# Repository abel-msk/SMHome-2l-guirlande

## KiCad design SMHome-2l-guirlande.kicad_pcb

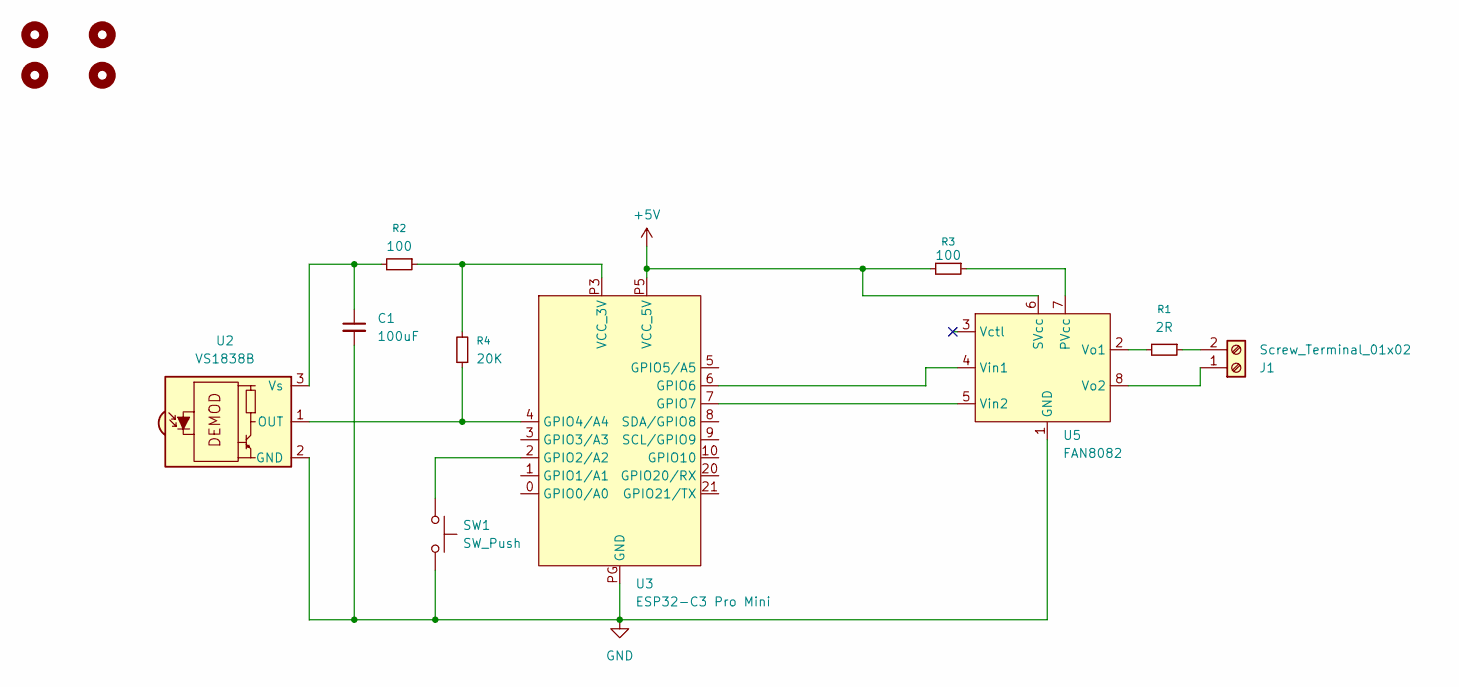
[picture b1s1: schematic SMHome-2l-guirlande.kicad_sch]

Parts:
C1: 100uF; C_1206_3216Metric_Pad1.33x1.80mm_HandSolder
J1: Screw_Terminal_01x02; TerminalBlock_Phoenix_MKDS-1,5-2_1x02_P5.00mm_Horizontal
R1: 2R; R_1210_3225Metric
R2: 100; R_0805_2012Metric_Pad1.20x1.40mm_HandSolder
R3: 100; R_1210_3225Metric_Pad1.30x2.65mm_HandSolder
R4: 20K; R_0805_2012Metric_Pad1.20x1.40mm_HandSolder
SW1: SW_Push; SW_SPST_TL3305A
TP1, TP2, TP3, TP4: MountingHole_2.5mm
U2: VS1838B; Vishay_MOLD-3Pin
U3: ESP32-C3 Pro Mini; ESP32-C3_Pro_mini_pin
U5: FAN8082; DIP-8_W10.16mm

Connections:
+5V: R3.2, U3.P5 (VCC_5V), U5.6 (SVcc)
GND: C1.2, SW1.2, U2.2 (GND), U3.PG (GND), U5.1 (GND)
unnamed: J1.1, U5.8 (Vo2)
unnamed: J1.2, R1.1
unnamed: R4.1, U2.1 (OUT), U3.4 (GPIO4/A4)
unnamed: C1.1, R2.2, U2.3 (Vs)
unnamed: SW1.1, U3.2 (GPIO2/A2)
unnamed: U3.6 (GPIO6), U5.4 (Vin1)
unnamed: U3.7 (GPIO7), U5.5 (Vin2)
unnamed: R2.1, R4.2, U3.P3 (VCC_3V)
unnamed: R3.1, U5.7 (PVcc)
unnamed: R1.2, U5.2 (Vo1)

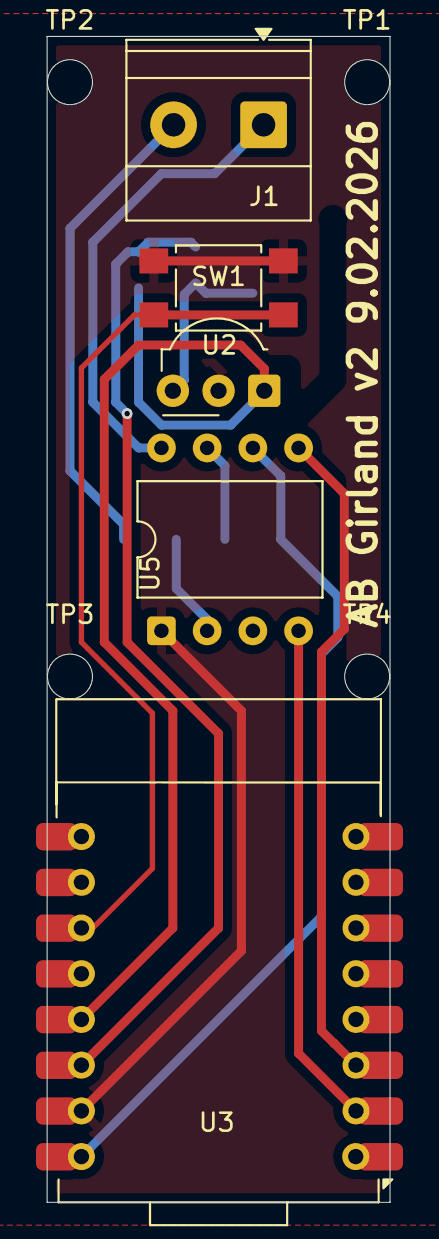
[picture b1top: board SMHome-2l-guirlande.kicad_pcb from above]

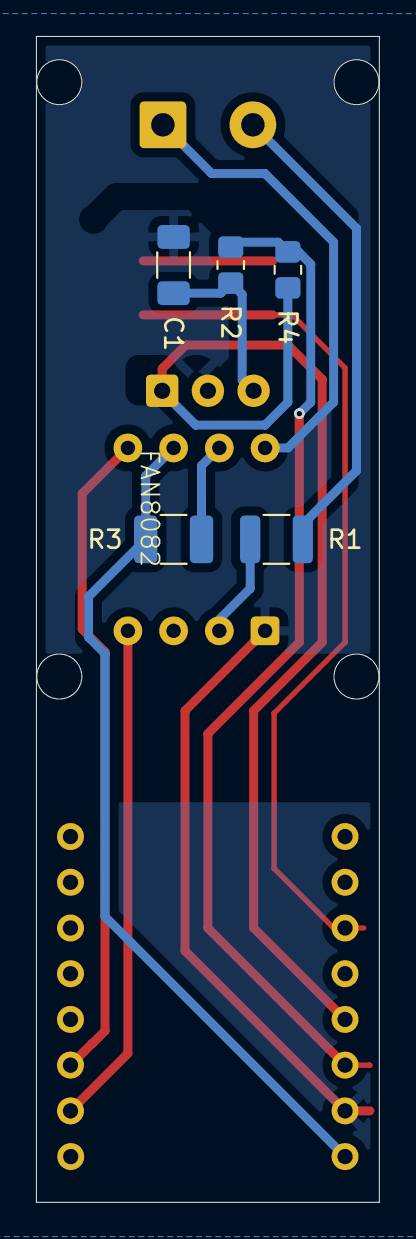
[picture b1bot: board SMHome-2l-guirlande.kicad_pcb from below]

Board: 2 copper layers, 19.0 x 64.8 mm, 14 parts (5 on the bottom side), 12 nets.

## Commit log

2025-12-22 Release
2026-02-09 Decrease size. Center BTN
2026-02-09 Make assemble documents. make narrower
2026-02-09 Fix mounting holes. Move sensor
